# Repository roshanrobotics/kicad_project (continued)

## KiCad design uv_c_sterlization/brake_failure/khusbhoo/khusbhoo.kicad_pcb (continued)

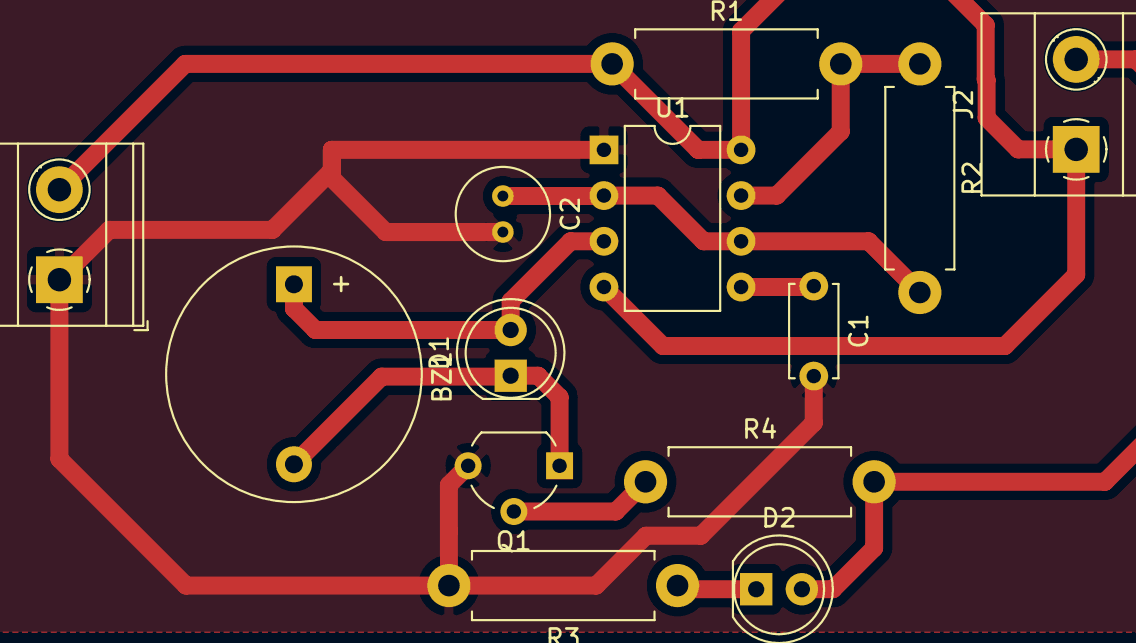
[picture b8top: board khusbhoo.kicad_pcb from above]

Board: 2 copper layers, 13 parts (0 on the bottom side), 10 nets.

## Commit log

2023-09-01 Kicad_project_2021
    kicad_project_list
